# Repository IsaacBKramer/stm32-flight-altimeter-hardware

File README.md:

# stm32-flight-altimeter-hardware

Autodesk Eagle schematics and board design files for the stm32 flight altimeter. This design features an STM32 microcontroller with a barometer, 9DOF 
accelerometer/gyroscope/magnetometer, and flash memory. It also has a 3.3V regulator

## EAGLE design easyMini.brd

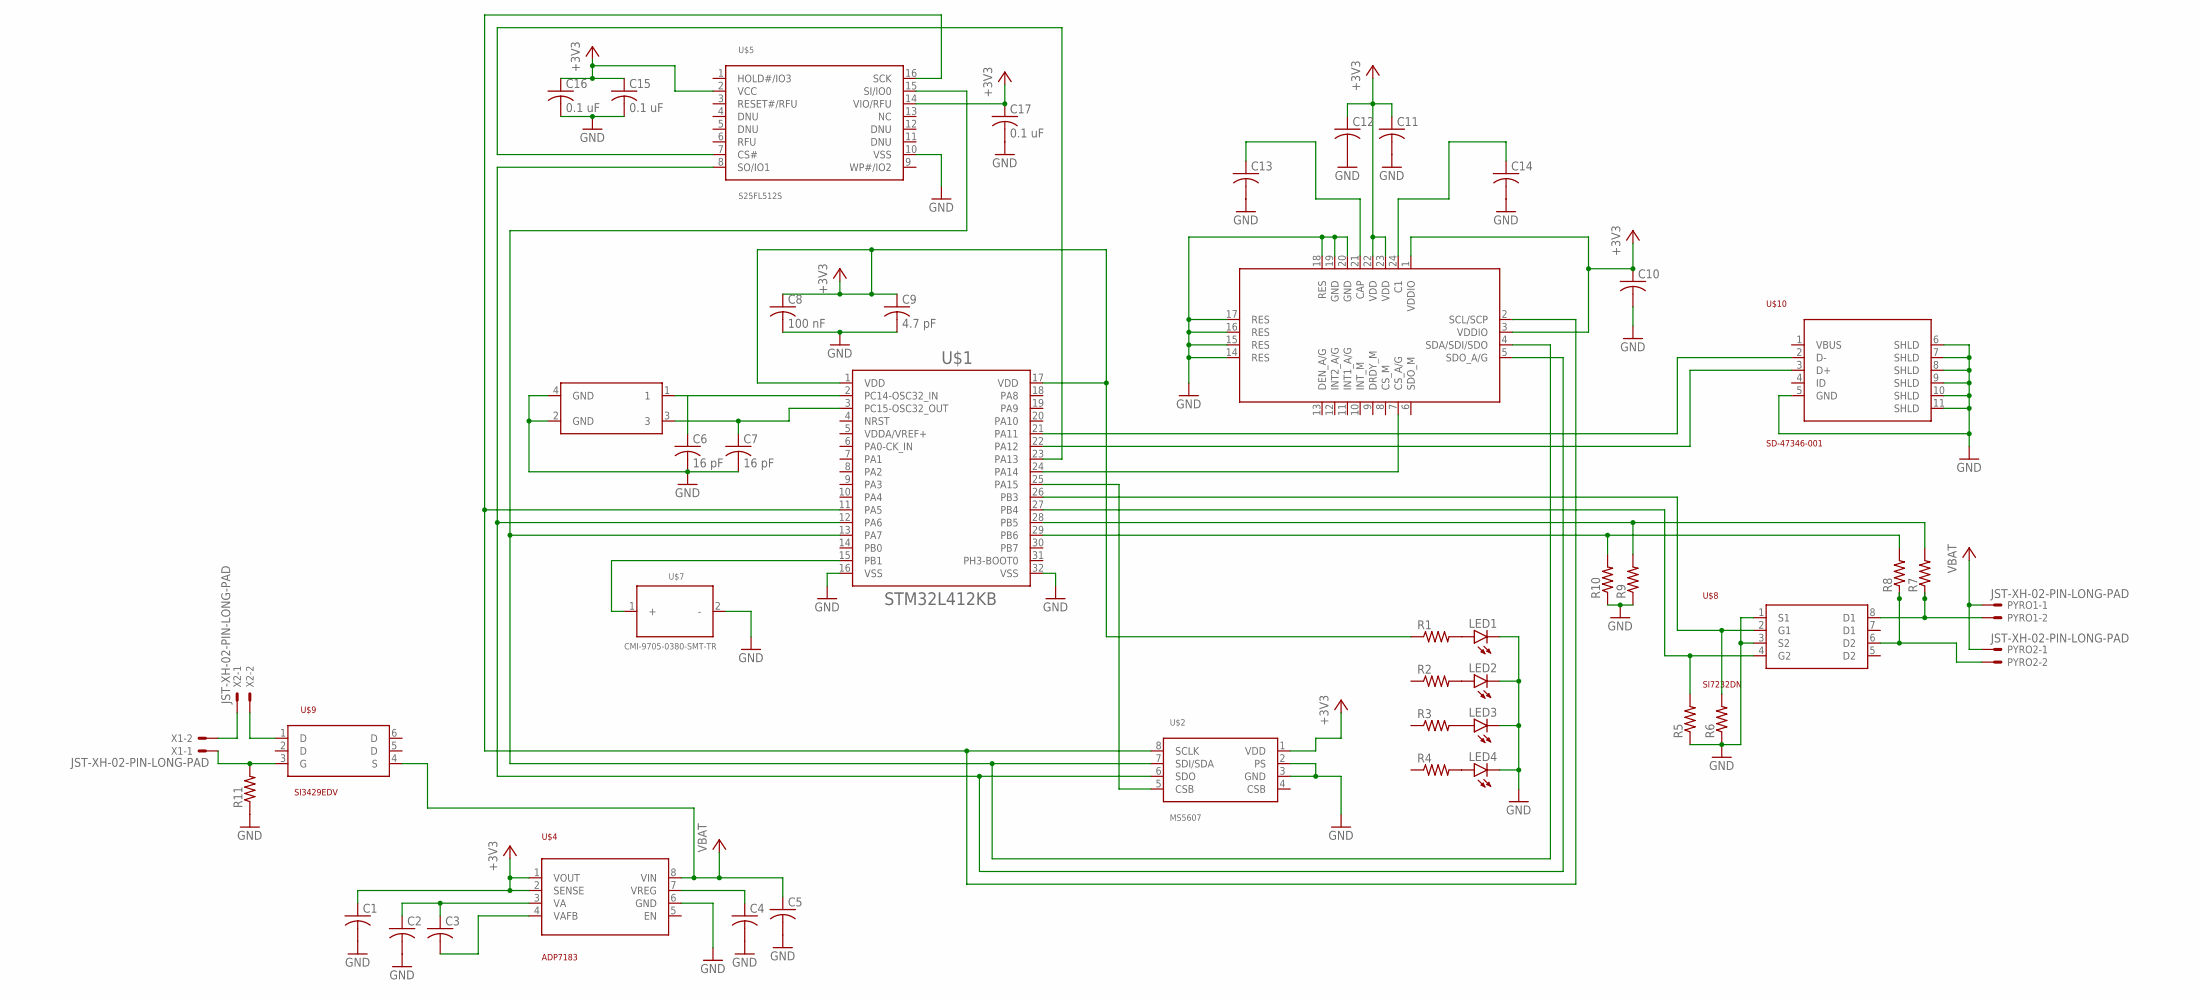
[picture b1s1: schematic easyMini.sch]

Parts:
C1, C2, C3, C4, C5, C10, C11, C12, C13, C14: C-USC0805; C0805
C6, C7: 16 pF; C0805
C8: 100 nF; C0805
C9: 4.7 pF; C0805
C15, C16, C17: 0.1 uF; C0805
LED1, LED2, LED3, LED4: LED; SMARTLED-TTW
PYRO1, PYRO2: JST-XH-02-PIN-LONG-PAD; JST-XH-02-PACKAGE-LONG-PAD
R1, R2, R3, R4, R5, R6, R7, R8, R9, R10, R11: R-US_M0805; M0805
U$1: STM32L412KB; LQFP32
U$2: MS5607
U$3: LSM9DS1
U$4: ADP7183
U$5: S25FL512S
U$6: SXT1148FE48-24.000MT; SXT114
U$7: CMI-9705-0380-SMT-TR
U$8: SI7232DN
U$9: SI3429EDV
U$10: SD-47346-001
X1, X2: JST-XH-02-PIN-LONG-PAD; JST-XH-02-PACKAGE-LONG-PAD

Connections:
+3V3: C1.1, C8.1, C9.1, C10.1, C11.1, C12.1, C15.1, C16.1, C17.1, PYRO1.1, PYRO2.1, R1.1, U$1.1 (VDD), U$1.17 (VDD), U$2.1 (VDD), U$3.1 (VDDIO), U$3.3 (VDDIO), U$3.22 (VDD), U$3.23 (VDD), U$4.1 (VOUT), U$4.2 (SENSE), U$5.2 (VCC), U$5.14 (VIO/RFU)
GND: C1.2, C2.2, C4.2, C5.2, C6.2, C7.2, C8.2, C9.2, C10.2, C11.2, C12.2, C13.2, C14.2, C15.2, C16.2, C17.2, LED1.C@1 (C), LED2.C@1 (C), LED3.C@1 (C), LED4.C@1 (C), R5.1, R6.1, R9.1, R10.1, R11.1, U$1.16 (VSS), U$1.32 (VSS), U$2.2 (PS), U$2.3 (GND), U$3.14 (RES), U$3.15 (RES), U$3.16 (RES), U$3.17 (RES), U$3.18 (RES), U$3.19 (GND), U$3.20 (GND), U$4.6 (GND), U$5.10 (VSS), U$6.2 (GND), U$6.4 (GND), U$7.2 (-), U$8.1 (S1), U$8.3 (S2), U$10.5 (GND), U$10.6 (SHLD), U$10.7 (SHLD), U$10.8 (SHLD), U$10.9 (SHLD), U$10.10 (SHLD), U$10.11 (SHLD)
unnamed: U$1.13 (PA7), U$2.7 (SDI/SDA), U$3.4 (SDA/SDI/SDO), U$5.15 (SI/IO0)
unnamed: U$1.11 (PA5), U$2.8 (SCLK), U$3.2 (SCL/SCP), U$5.16 (SCK)
unnamed: U$1.12 (PA6), U$2.6 (SDO), U$3.5 (SDO_A/G), U$5.8 (SO/IO1)
unnamed: C13.1, U$3.21 (CAP)
unnamed: C14.1, U$3.24 (C1)
unnamed: C2.1, C3.1, U$4.3 (VA)
unnamed: C4.1, U$4.7 (VREG)
unnamed: C3.2, U$4.4 (VAFB)
unnamed: U$1.23 (PA13), U$5.7 (CS#)
unnamed: LED1.A@1 (A), R1.2
unnamed: LED2.A@1 (A), R2.2
unnamed: LED3.A@1 (A), R3.2
unnamed: LED4.A@1 (A), R4.2
unnamed: PYRO1.2, R7.1, U$8.8 (D1)
unnamed: U$1.24 (PA14), U$3.7 (CS_A/G)
unnamed: U$1.25 (PA15), U$2.5 (CSB)
unnamed: PYRO2.2, R8.1, U$8.6 (D2)
unnamed: R6.2, U$1.26 (PB3), U$8.2 (G1)
unnamed: R5.2, U$1.27 (PB4), U$8.4 (G2)
unnamed: U$1.15 (PB1), U$7.1 (+)
unnamed: R7.2, R9.2, U$1.28 (PB5)
unnamed: R8.2, R10.2, U$1.29 (PB6)
unnamed: X1.2, X2.1
unnamed: C6.1, U$1.2 (PC14-OSC32_IN), U$6.1
unnamed: C7.1, U$1.3 (PC15-OSC32_OUT), U$6.3
unnamed: R11.2, U$9.3 (G), X1.1
unnamed: U$9.1 (D), X2.2
unnamed: U$1.21 (PA11), U$10.2 (D-)
unnamed: U$1.22 (PA12), U$10.3 (D+)
VCC: C5.1, U$4.8 (VIN), U$9.4 (S)

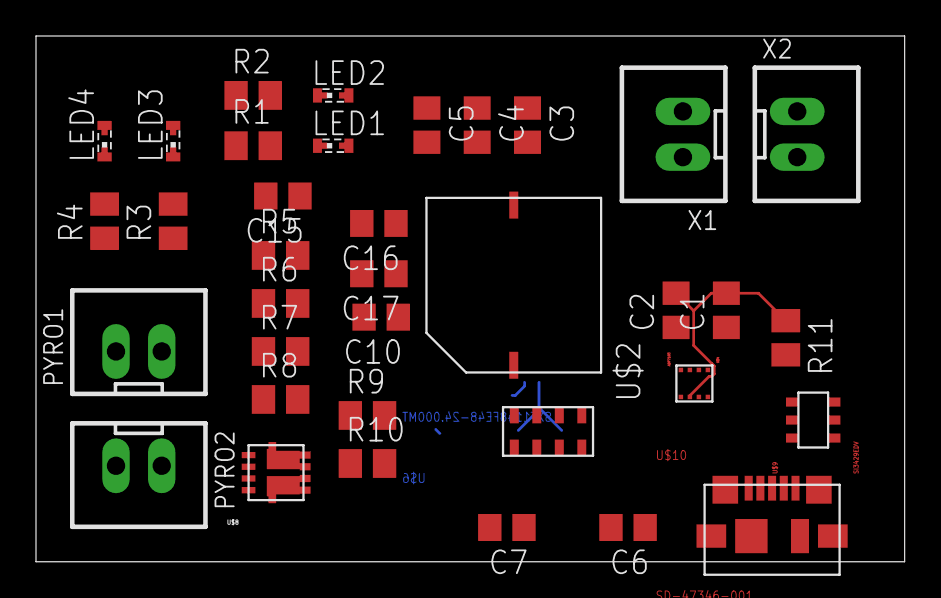
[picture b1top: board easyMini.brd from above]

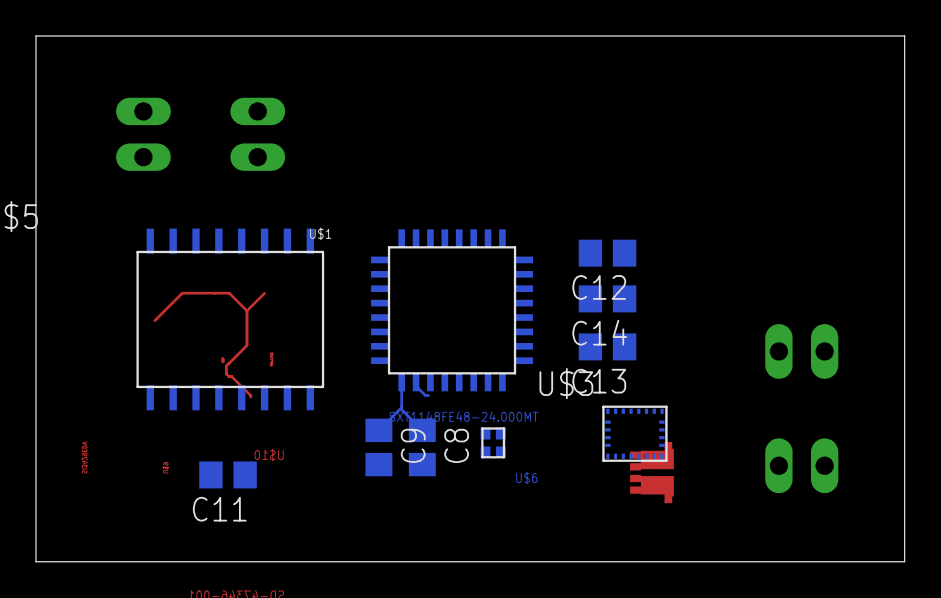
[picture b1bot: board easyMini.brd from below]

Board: 2 copper layers, 48.3 x 29.2 mm, 46 parts (10 on the bottom side), 32 nets.

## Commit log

2021-01-02 Visual adjustments
2021-01-02 Added board design
2021-01-03 Added pyro fets, resistors, and connectors. Modified board design to make more compact.
2021-01-03 Added reverse polarity protection and battery/switch connectors. Continued board design organization:
2021-01-04 Shrink board and organization of two layers into more sensible layout. Changed pins to allow USB addition on microcontroller.
